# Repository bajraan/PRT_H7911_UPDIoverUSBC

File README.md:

<!-- Begin README -->

<h1 align="center">UPDI over USB-C</h1>

<p align="center">
    
    </br>
    </br>

</p>
</br>
</br>

<p align="center">
    
    <br>
</p>

</br>
</br>
<div align="center">

</div>

</br>
</br>

## Content  [Project Utilization]

- [Features](##Features)
- [Diagram](##Diagram)
- [Use Case 1](##UseCase1)
- [Use Case 2](##UseCase2)

## Content [Project Development]

- [Workflow](##Workflow)
- [Software](##Software)

## Features
```markdown
1. Programing target sample over USB-C cable interface
2. Compatible with MICROCHIP PicKit 4 programmer
3. Powering target device over USB-C cable interface
4. Wide capabilities of power connectors
```
## Diagram
## Use Case 1
## Use Case 2

## Software
```markdown
[KiCAD](https://www.kicad.org/)
[FreeCAD](https://www.freecad.org/)
[FreeCAD][Kicad Step UP]()
[KiCAD][fabrication toolkig]()
```

## Workflow
```markdown
1. KiCAD  [/KiCAD_H7911_MAIN] Create PCB as a Panel

2. KiCAD  [/KiCAD_H7911_MAIN] export to KiCAD_Export_H7911-PCB-1over2
3. KiCAD  [/KiCAD_H7911_MAIN] export to KiCAD_Export_H7911-PCB-2over2

4. KiCAD  KiCAD_Export_H7911-PCB-1over2 prepare and export silkscreen
5. KiCAD  KiCAD_Export_H7911-PCB-2over2 prepare and export silkscreen

6. Import PCB to FreeCAD using KiCAD Step Up WorkBench

    1. FreeCAD  [/FreeCAD] import .kicad_pcb shape 1over2
    2. FreeCAD  [/FreeCAD] import .kicad_pcb tracks 1over2
    3. FreeCAD  [/FreeCAD] import .dxf silkscreen 1over2
    4. FreeCAD  [/FreeCAD] import .kicad_pcb shape 2over2
    5. FreeCAD  [/FreeCAD] import .kicad_pcb tracks 2over2
    6. FreeCAD  [/FreeCAD] import .dxf silkscreen 2over2

7. FreeCAD  [/FreeCAD] Move pcb 1over2 to the correnct place
8. FreeCAD  [/FreeCAD] Housing desing based on PCB shapes
9. FreeCAD  [/FreeCAD] Export housing shape to the .stl file
10. KiCAD  [/KiCAD_H7911_MAIN] Export fabrication data
11. KiCAD  [/KiCAD_H7911_MAIN] Order PCB for example from jlcpcb.com 
```
## helping re-sources

https://www.youtube.com/watch?v=b3NoAOxOGxA

## Workflow Examples

**_KiCAD_Export_H7911-PCB-1over2 prepare and export silkscreen_**
<br/>

-------------------
<br/>

> [!NOTE] 
>**_KiCAD_Export_H7911-PCB-1over2 prepare and export silkscreen_**
<br/>

-------------------

> [!NOTE] 
> Exporting PCB
> Import PCB to FreeCAD using KiCAD Step Up WorkBench
Move pcb 1over2 to the correnct place
Housing desing based on PCB shapes
Export housing shape to the .stl file
KiCAD_H7911_MAIN Export fabrication data
Order PCB for example from jlcpcb.com
Cutting Panel PCB

## PCB panel view

## Images
```markdown

```
 <br>

*Add #gh-light-mode-only or #gh-dark-mode-only to the end of the image link to make it only visible in light or dark mode, respectively.*

## Code: 
test item
### Inline code:

```markdown
Here is `inline code`.
```
Here is `inline code`.

### Block code without syntax highlighting:

```markdown
```This is a block of code.```
```
```
This is a block of code.
```

### Block code with syntax highlighting:

```markdown
```python 
print("Hello, world!")
```

```python
print("Hello, world!")
```

## Tables

```markdown
| Header One     | Header Two     |
| -------------- | -------------- |
| Content Cell 1 | Content Cell 2 |
| Content Cell 3 | Content Cell 4 |
```
| Header One     | Header Two     |
| -------------- | -------------- |
| Content Cell 1 | Content Cell 2 |
| Content Cell 3 | Content Cell 4 |

## Horizontal Rules

Use three or more dashes, asterisks, or underscores:

```markdown
---
***
___
```
---
***
___

## Blockquotes

``` markdown
> This is a blockquote.
>
> > This is a nested blockquote.
```
> This is a blockquote.
>
> > This is a nested blockquote.

## Escaping Characters
## Task Lists
### Alerts

GitHub Flavored Markdown supports alerts that can be used to highlight important information:

```markdown
  > [!NOTE]  
  > Highlights information that users should take into account, even when skimming.

  > [!TIP]
  > Optional information to help a user be more successful.

  > [!IMPORTANT]  
  > Crucial information necessary for users to succeed.

  > [!WARNING]  
  > Critical content demanding immediate user attention due to potential risks.

  > [!CAUTION]
  > Negative potential consequences of an action.
```

> [!NOTE]  
> Highlights information that users should take into account, even when skimming.

> [!TIP]
> Optional information to help a user be more successful.

> [!IMPORTANT]  
> Crucial information necessary for users to succeed.

> [!WARNING]  
> Critical content demanding immediate user attention due to potential risks.

> [!CAUTION]
> Negative potential consequences of an action.

## Closing

Remember, not all of these features are supported in every Markdown processor. Always check your specific processor's documentation for supported features.

You can use this as a README for your repository. Feel free to expand and improve the guide to better fit your requirements or to add more advanced features. Also, feel free to contribute and expand this guide for better community knowledge.

## Resources

- [Markdown Guide](https://www.markdownguide.org/) - A free and open-source reference guide that explains how to use Markdown.
- [Daring Fireball](https://daringfireball.net/projects/markdown/) - The original Markdown project by John Gruber.
- [GitHub Flavored Markdown](https://github.github.com/gfm/) - GitHub's variant of Markdown, which includes features like task lists and tables.
- [CommonMark](https://commonmark.org/) - A strong specification of Markdown, designed to clarify many edge cases and inconsistencies in the original Markdown specification.
- [Markdown Cheatsheet](https://github.com/adam-p/markdown-here/wiki/Markdown-Cheatsheet) - A quick reference to Markdown syntax.
- [Pandoc](https://pandoc.org/) - A universal document converter that supports Markdown and many other markup languages.
- [StackEdit](https://stackedit.io/) - An in-browser Markdown editor.
- [Markdown Tutorial](https://chat.openai.com/?model=gpt-4#:~:text=browser%20Markdown%20editor.-,Markdown%20Tutorial,-%3A%20An%20interactive%20tutorial) - An interactive tutorial to learn Markdown.
- [Jupyter Notebook](https://jupyter.org/) - Although not strictly a Markdown resource, Jupyter Notebooks use Markdown for all non-code cells, making it a useful tool for scientific documentation where code and commentary are intermixed.
- [GitHub Markdown Alerts](https://blog.jakelee.co.uk/github-alert-experiments/) - A blog post that discusses the use of GitHub Markdown Alerts
- [GitHub Markdown Alerts Discussion](https://github.com/orgs/community/discussions/16925) - A GitHub discussion that discusses the use of GitHub Markdown Alerts

## License

This project is released under the terms of the **MIT License**, which permits use, modification, and distribution of the code, subject to the conditions outlined in the license.
- The [MIT License](https://choosealicense.com/licenses/mit/) provides certain freedoms while preserving rights of attribution to the original creators.
- For more details, see the [LICENSE](LICENSE) file in this repository. in this repository.

## Credits

**Author:** [Scott Grivner](https://github.com/scottgriv) <br>
**Email:** [scott.grivner@gmail.com](mailto:scott.grivner@gmail.com) <br>
**Website:** [scottgrivner.dev](https://www.scottgrivner.dev) <br>
**Reference:** [Main Branch](https://github.com/scottgriv/markdown-demo) <br>

---------------

<div align="center">
    
</div>

<!-- End README -->

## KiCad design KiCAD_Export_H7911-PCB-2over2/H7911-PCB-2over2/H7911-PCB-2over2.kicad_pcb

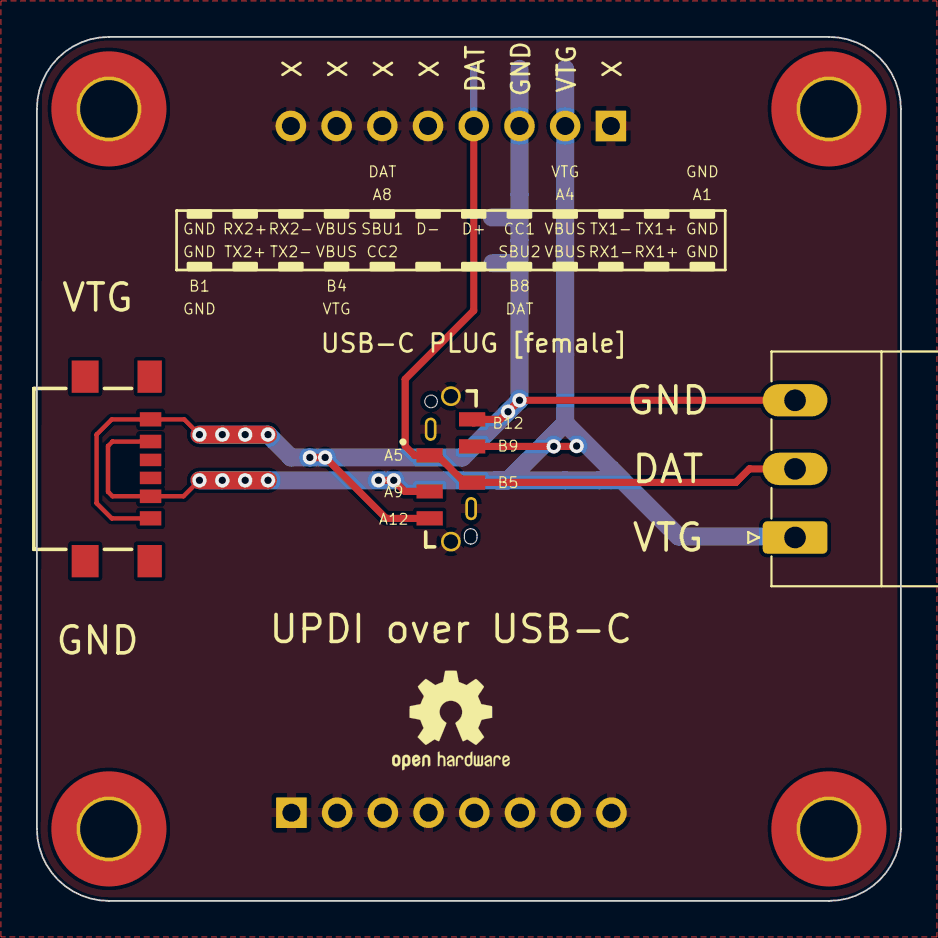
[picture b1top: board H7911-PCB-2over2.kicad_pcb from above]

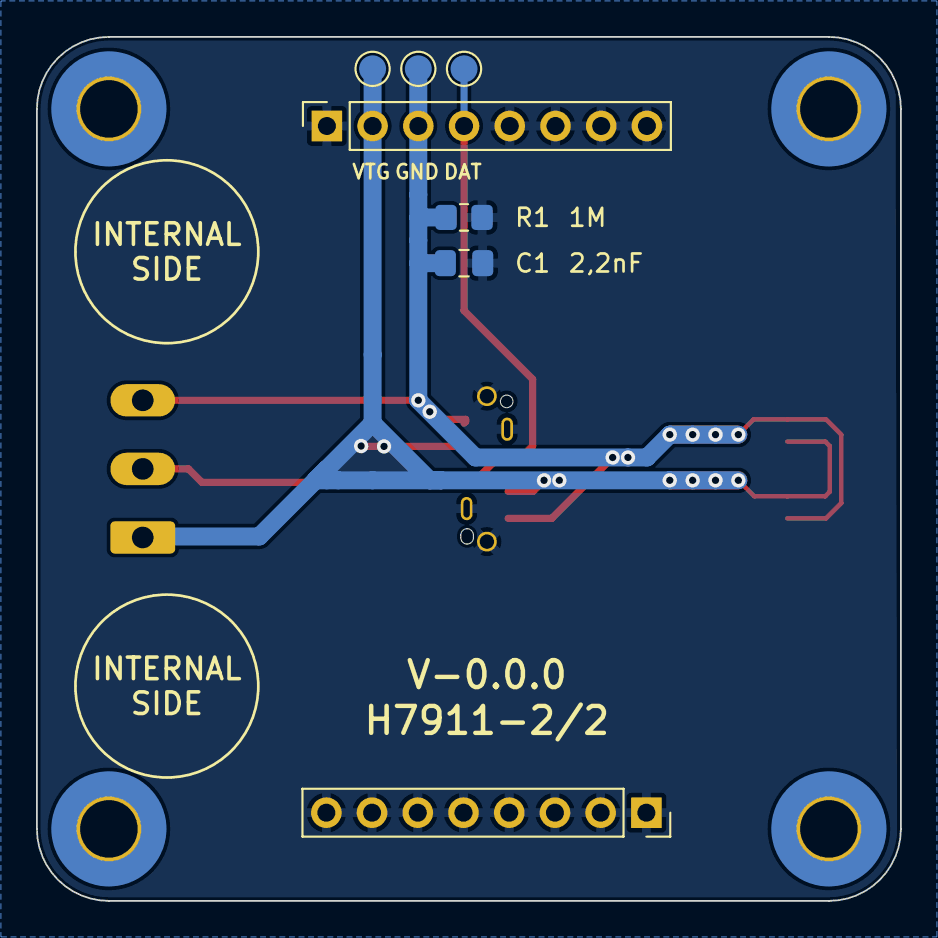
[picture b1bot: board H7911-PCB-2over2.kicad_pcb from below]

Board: 2 copper layers, 48.0 x 48.0 mm, 14 parts (7 on the bottom side), 4 nets.

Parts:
C1: 2,2nF; C_0805_2012Metric_Pad1.18x1.45mm_HandSolder
H5, H6, H7, H8: MountingHole; MountingHole_3.2mm_M3_Pad_TopBottom
J2: USB4180-03-0120-C_REVA; GCT_USB4180-03-0120-C_REVA
J5, J9: CON; PinSocket_1x08_P2.54mm_Vertical
J8: Conn_01x03_Pin; PhoenixContact_MC_1,5_3-G-3.81_1x03_P3.81mm_Horizontal
J12: USB4135-GF-A_REVA; GCT_USB4135-GF-A_REVA
R1: 1M; R_0805_2012Metric_Pad1.20x1.40mm_HandSolder
TP1, TP2, TP3: TestPoint; TestPoint_Pad_D1.5mm

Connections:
/Slave/Slave_DAT: J2.A5 (CC1), J2.B5 (CC2), J5.4, J8.2, TP1.1
/Slave/Slave_GND: C1.1, J2.A12 (GND_A), J2.B12 (GND_B), J5.3, J8.3, J12.A12 (GND_A), J12.B12 (GND_B), R1.1, TP2.1
/Slave/Slave_VTG: J2.A9 (VBUS_A), J2.B9 (VBUS_B), J5.2, J8.1, J12.A9 (VBUS_A), J12.B9 (VBUS_B), TP3.1
GND: C1.2, J2.S1 (SHIELD), J2.S2 (SHIELD), J2.S3 (SHIELD), J2.S4 (SHIELD), J5.1, J5.5, J5.6, J5.7, J5.8, J9.1, J9.2, J9.3, J9.4, J9.5, J9.6, J9.7, J9.8, R1.2

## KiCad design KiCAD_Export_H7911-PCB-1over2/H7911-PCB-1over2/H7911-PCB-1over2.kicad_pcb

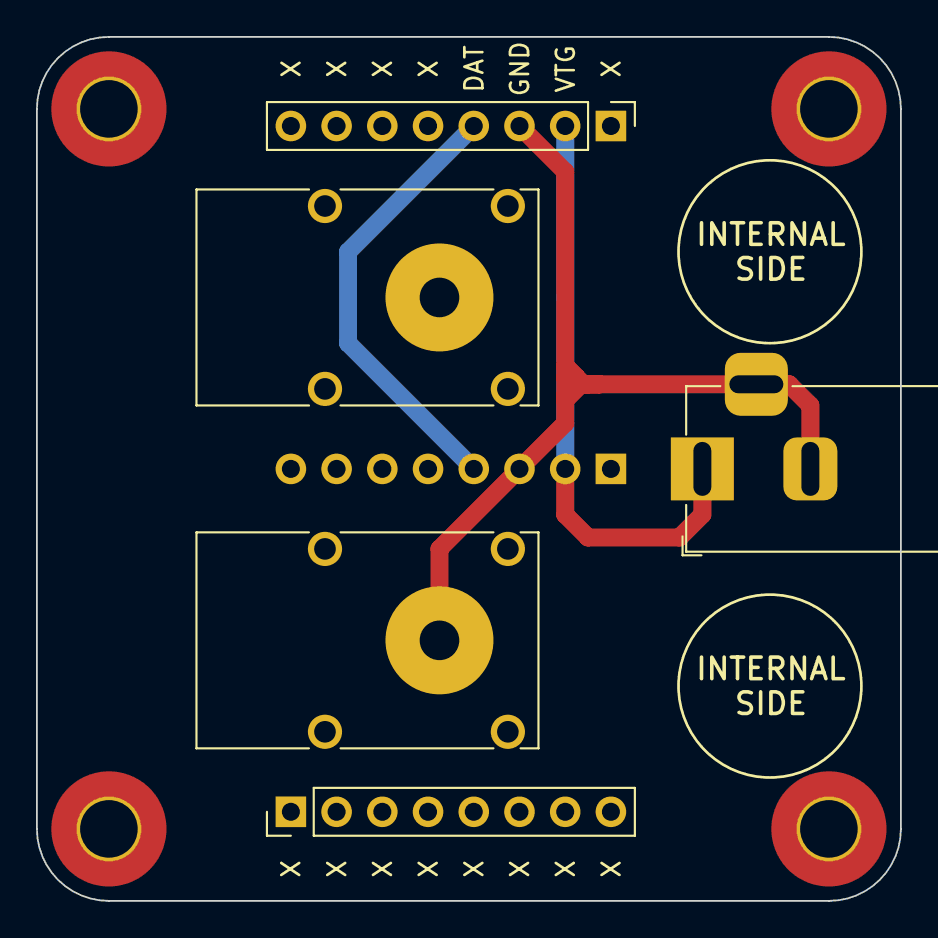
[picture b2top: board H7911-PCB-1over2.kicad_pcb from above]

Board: 2 copper layers, 48.0 x 48.0 mm, 10 parts (1 on the bottom side), 3 nets.

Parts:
H1, H2, H3, H4: MountingHole; MountingHole_3.2mm_M3_Pad_TopBottom
J1: PicKit; PinHeader_1x08_P2.54mm_Vertical
J3, J4: CON; PinHeader_1x08_P2.54mm_Vertical
J6: SWEB 8094 RED
J7: SWEB 8094 BLACK
J10: Barrel_Jack_Switch; BarrelJack_Horizontal

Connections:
/Master/Master_DAT: J1.4, J4.4
/Master/Master_GND: J1.3, J4.3, J7.1, J10.2, J10.3
/Master/Master_VTG: J1.2, J4.2, J6.1, J10.1

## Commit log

2024-03-19 fresh commit
2024-03-19 files path change
2024-03-19 readme.md update
2024-03-21 readme.md format testing
2024-03-21 reedme.md update
